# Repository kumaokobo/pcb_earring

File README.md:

# pcb_earring
An earring design using PCB can be chained.

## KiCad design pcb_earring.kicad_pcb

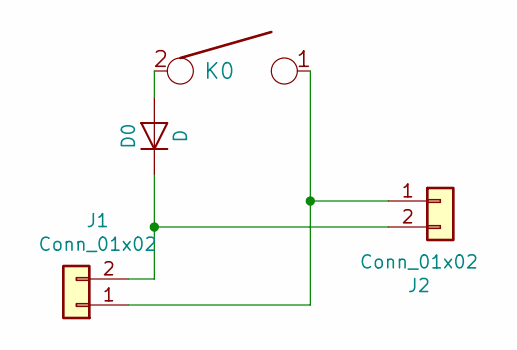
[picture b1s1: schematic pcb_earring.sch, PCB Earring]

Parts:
D0: D; Diode-dual
J1, J2: Conn_01x02; PinHeader_1x02_P2.54mm_Vertical
K0: KEYSW; Mx_Alps_100-dualside

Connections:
unnamed: D0.1 (K), J1.2, J2.2
unnamed: D0.2 (A), K0.2
unnamed: J1.1, J2.1, K0.1

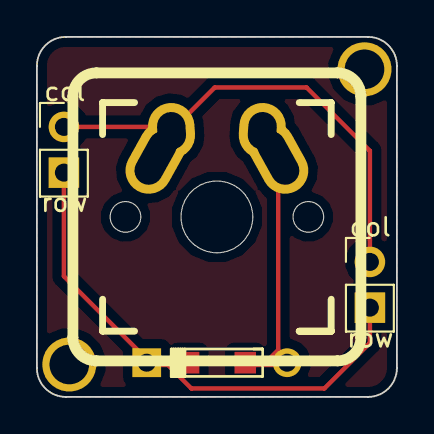
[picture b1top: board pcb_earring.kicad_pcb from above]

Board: 2 copper layers, 20.0 x 20.0 mm, 6 parts (0 on the bottom side), 3 nets.

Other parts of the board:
HOLE_M2, HOLE_M2#2: VAL**; HOLE_M2

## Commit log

2020-03-14 Add pcb design (#1)
    * Added .gitignore
    * Added footprints.
    * Added KiCad files.
    * Added images.
    * Added a script to rename gerber files.
